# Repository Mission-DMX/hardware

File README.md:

# hardware
This repository contains documentations, pcb designs and fpga designs of the console

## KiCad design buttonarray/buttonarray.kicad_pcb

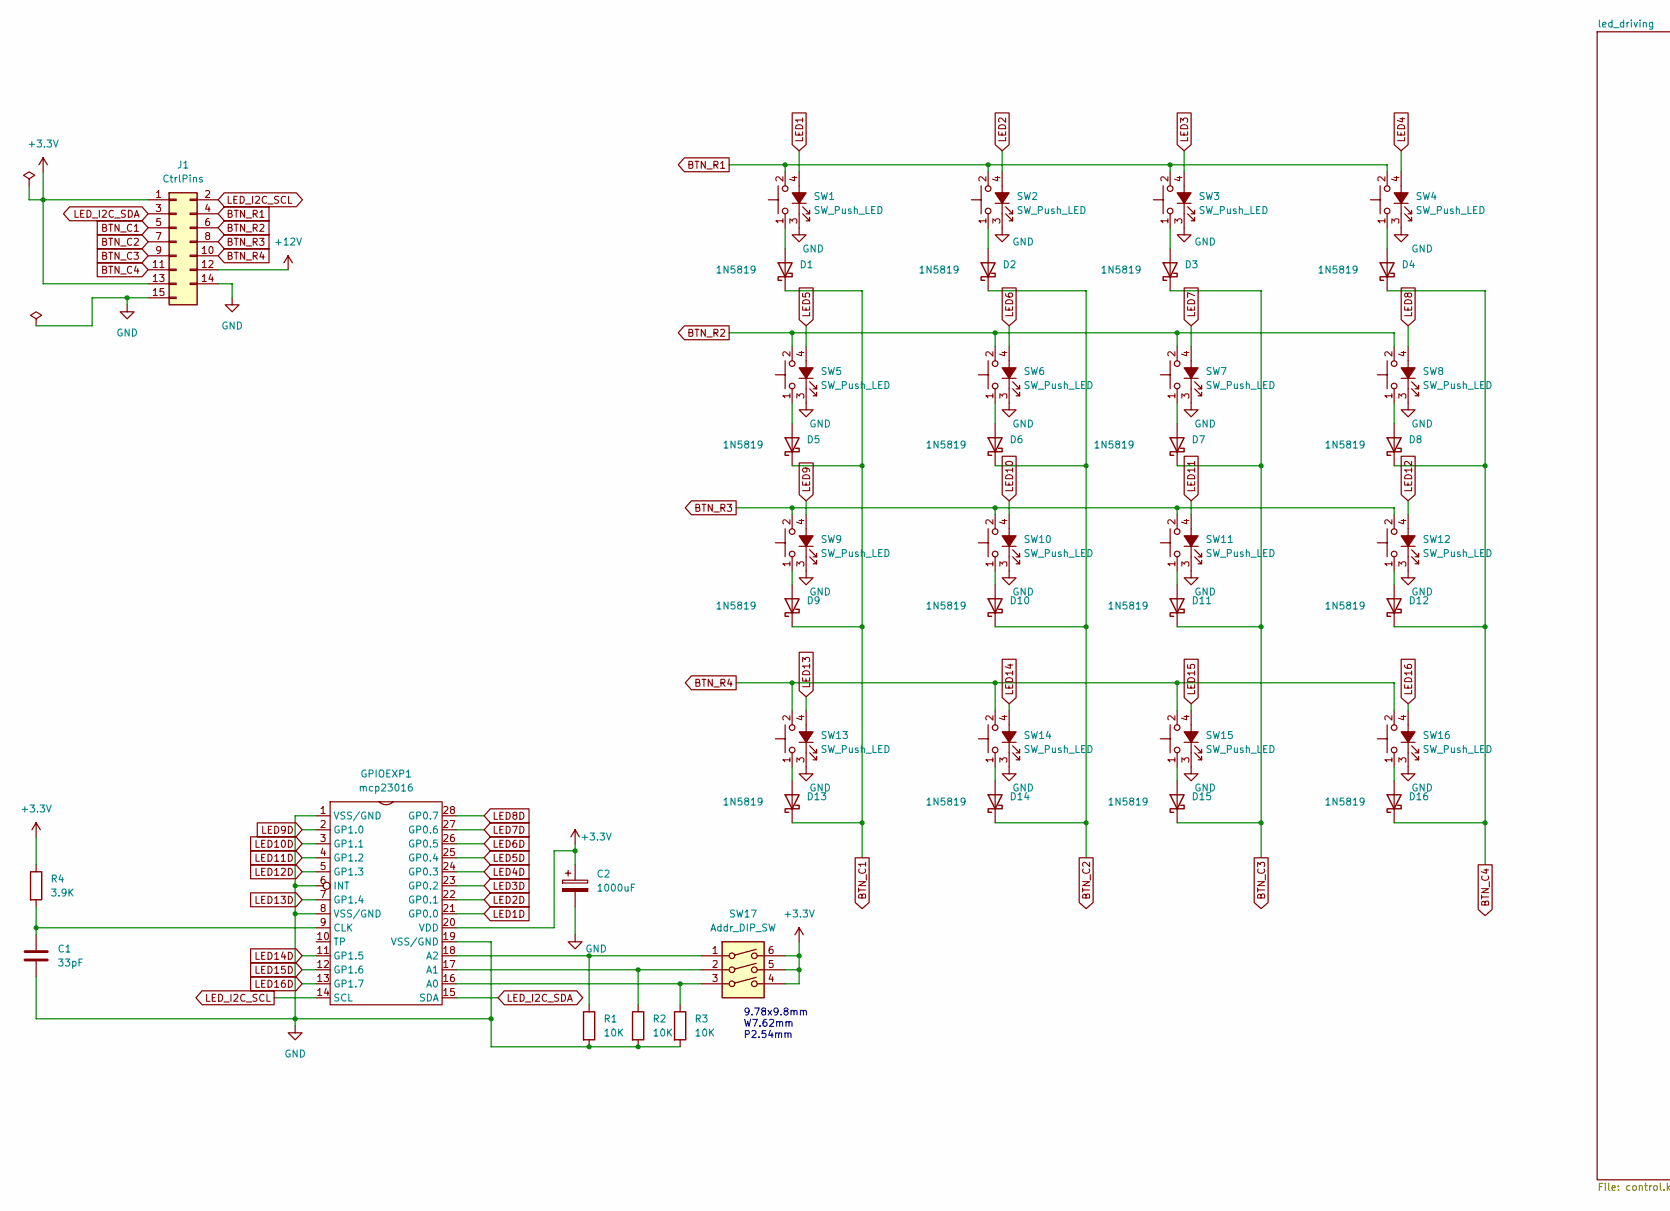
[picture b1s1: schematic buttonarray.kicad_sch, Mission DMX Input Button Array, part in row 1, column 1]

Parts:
C1: 33pF; C_1206_3216Metric_Pad1.33x1.80mm_HandSolder
C2: 1000uF; CP_Radial_D13.0mm_P5.00mm
D1, D2, D3, D4, D5, D6, D7, D8, D9, D10, D11, D12, D13, D14, D15, D16: 1N5819; D_DO-41_SOD81_P10.16mm_Horizontal
GPIOEXP1: mcp23016
J1: CtrlPins; IDC-Header_2x08_P2.54mm_Latch_Vertical
R1, R2, R3: 10K; R_0805_2012Metric_Pad1.20x1.40mm_HandSolder
R4: 3.9K; R_0603_1608Metric_Pad0.98x0.95mm_HandSolder
SW1, SW2, SW3, SW4, SW5, SW6, SW7, SW8, SW9, SW10, SW11, SW12, SW13, SW14, SW15, SW16: SW_Push_LED; MXOnly-1U
SW17: Addr_DIP_SW; SW_DIP_SPSTx03_Slide_9.78x9.8mm_W7.62mm_P2.54mm

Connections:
+3V3: C2.1, GPIOEXP1.20 (VDD), J1.1, J1.13, R4.1, SW17.4, SW17.5, SW17.6; also elsewhere on the board
+12V: J1.12; also elsewhere on the board
BTN_C1: D1.1 (K), D5.1 (K), D9.1 (K), D13.1 (K), J1.5
BTN_C2: D2.1 (K), D6.1 (K), D10.1 (K), D14.1 (K), J1.7
BTN_C3: D3.1 (K), D7.1 (K), D11.1 (K), D15.1 (K), J1.9
BTN_C4: D4.1 (K), D8.1 (K), D12.1 (K), D16.1 (K), J1.11
BTN_R1: J1.4, SW1.2, SW2.2, SW3.2, SW4.2
BTN_R2: J1.6, SW5.2, SW6.2, SW7.2, SW8.2
BTN_R3: J1.8, SW9.2, SW10.2, SW11.2, SW12.2
BTN_R4: J1.10, SW13.2, SW14.2, SW15.2, SW16.2
GND: C1.2, C2.2, GPIOEXP1.1 (VSS/GND), GPIOEXP1.6 (INT), GPIOEXP1.8 (VSS/GND), GPIOEXP1.19 (VSS/GND), J1.14, J1.15, R1.2, R2.2, R3.2, SW1.3 (K), SW2.3 (K), SW3.3 (K), SW4.3 (K), SW5.3 (K), SW6.3 (K), SW7.3 (K), SW8.3 (K), SW9.3 (K), SW10.3 (K), SW11.3 (K), SW12.3 (K), SW13.3 (K), SW14.3 (K), SW15.3 (K), SW16.3 (K); also elsewhere on the board
LED1: SW1.4 (A); also elsewhere on the board
LED1D: GPIOEXP1.21 (GP0.0); also elsewhere on the board
LED2: SW2.4 (A); also elsewhere on the board
LED2D: GPIOEXP1.22 (GP0.1); also elsewhere on the board
LED3: SW3.4 (A); also elsewhere on the board
LED3D: GPIOEXP1.23 (GP0.2); also elsewhere on the board
LED4: SW4.4 (A); also elsewhere on the board
LED4D: GPIOEXP1.24 (GP0.3); also elsewhere on the board
LED5: SW5.4 (A); also elsewhere on the board
LED5D: GPIOEXP1.25 (GP0.4); also elsewhere on the board
LED6: SW6.4 (A); also elsewhere on the board
LED6D: GPIOEXP1.26 (GP0.5); also elsewhere on the board
LED7: SW7.4 (A); also elsewhere on the board
LED7D: GPIOEXP1.27 (GP0.6); also elsewhere on the board
LED8: SW8.4 (A); also elsewhere on the board
LED8D: GPIOEXP1.28 (GP0.7); also elsewhere on the board
LED9: SW9.4 (A); also elsewhere on the board
LED9D: GPIOEXP1.2 (GP1.0); also elsewhere on the board
LED10: SW10.4 (A); also elsewhere on the board
LED10D: GPIOEXP1.3 (GP1.1); also elsewhere on the board
LED11: SW11.4 (A); also elsewhere on the board
LED11D: GPIOEXP1.4 (GP1.2); also elsewhere on the board
LED12: SW12.4 (A); also elsewhere on the board
LED12D: GPIOEXP1.5 (GP1.3); also elsewhere on the board
LED13: SW13.4 (A); also elsewhere on the board
LED13D: GPIOEXP1.7 (GP1.4); also elsewhere on the board
LED14: SW14.4 (A); also elsewhere on the board
LED14D: GPIOEXP1.11 (GP1.5); also elsewhere on the board
LED15: SW15.4 (A); also elsewhere on the board
LED15D: GPIOEXP1.12 (GP1.6); also elsewhere on the board
LED16: SW16.4 (A); also elsewhere on the board
LED16D: GPIOEXP1.13 (GP1.7); also elsewhere on the board
LED_I2C_SCL: GPIOEXP1.14 (SCL), J1.2
LED_I2C_SDA: GPIOEXP1.15 (SDA), J1.3
unnamed: C1.1, GPIOEXP1.9 (CLK), R4.2
unnamed: D1.2 (A), SW1.1
unnamed: D2.2 (A), SW2.1
unnamed: D3.2 (A), SW3.1
unnamed: D4.2 (A), SW4.1
unnamed: D5.2 (A), SW5.1
unnamed: D6.2 (A), SW6.1
unnamed: D7.2 (A), SW7.1
unnamed: D8.2 (A), SW8.1
unnamed: D9.2 (A), SW9.1
unnamed: D10.2 (A), SW10.1
unnamed: D11.2 (A), SW11.1
unnamed: D12.2 (A), SW12.1
unnamed: D13.2 (A), SW13.1
unnamed: D14.2 (A), SW14.1
unnamed: D15.2 (A), SW15.1
unnamed: D16.2 (A), SW16.1
unnamed: GPIOEXP1.16 (A0), R3.1, SW17.3
unnamed: GPIOEXP1.17 (A1), R2.1, SW17.2
unnamed: GPIOEXP1.18 (A2), R1.1, SW17.1

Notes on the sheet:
9.78x9.8mm W7.62mm P2.54mm

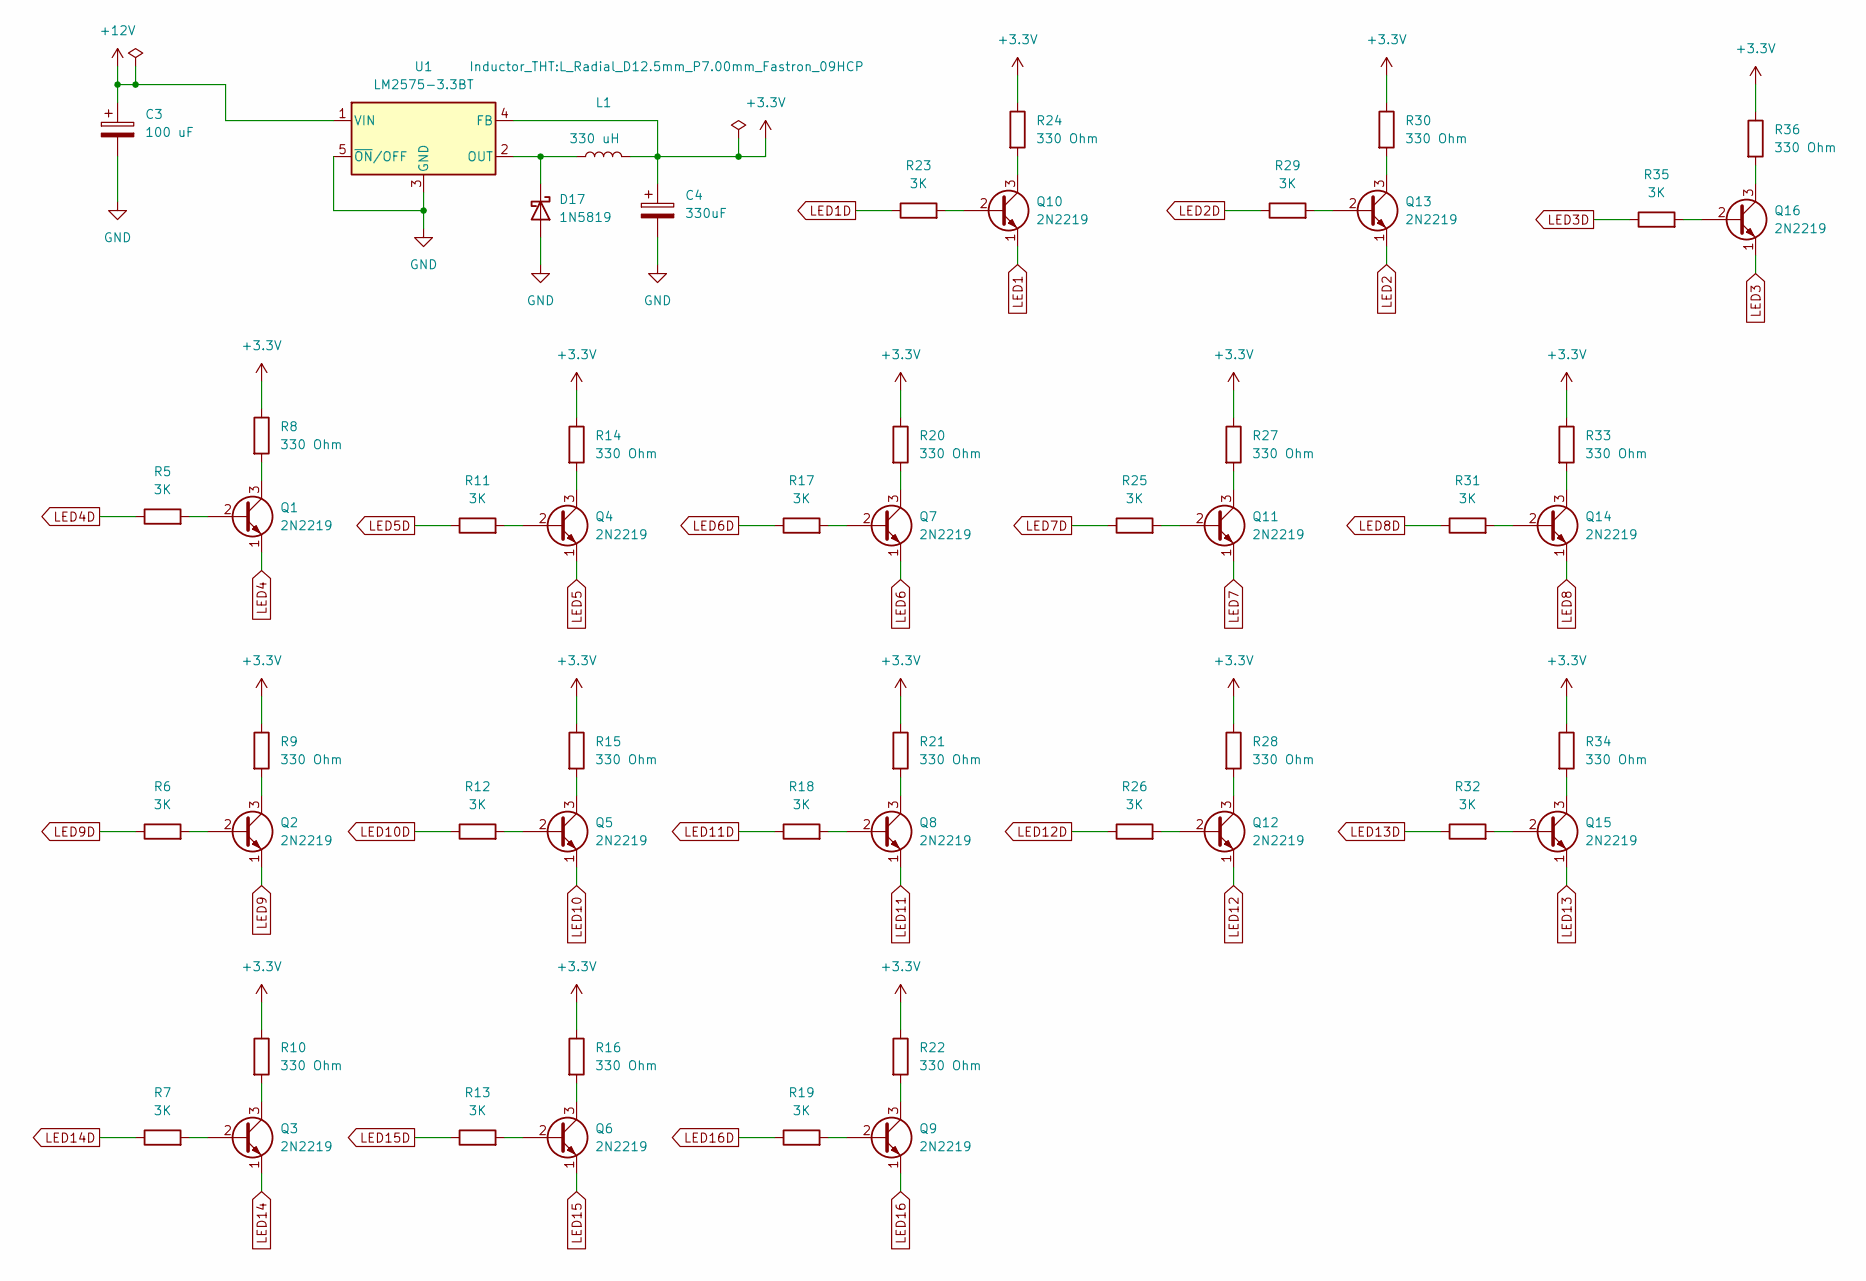
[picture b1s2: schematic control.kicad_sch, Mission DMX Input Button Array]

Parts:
C3: 100 uF; CP_Radial_D6.3mm_P2.50mm
C4: 330uF; CP_Radial_D10.0mm_P5.00mm
D17: 1N5819; D_DO-41_SOD81_P10.16mm_Horizontal
L1: 330 uH; L_Radial_D12.5mm_P7.00mm_Fastron_09HCP
Q1, Q2, Q3, Q4, Q5, Q6, Q7, Q8, Q9, Q10, Q11, Q12, Q13, Q14, Q15, Q16: 2N2219; TO-39-3
R5, R6, R7, R11, R12, R13, R17, R18, R19, R23, R25, R26, R29, R31, R32, R35: 3K; R_1206_3216Metric_Pad1.30x1.75mm_HandSolder
R8, R9, R10, R14, R15, R16, R20, R21, R22, R24, R27, R28, R30, R33, R34, R36: 330 Ohm; R_1206_3216Metric_Pad1.30x1.75mm_HandSolder
U1: LM2575-3.3BT; TO-220-5_Vertical

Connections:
+3V3: C4.1, L1.2, R8.1, R9.1, R10.1, R14.1, R15.1, R16.1, R20.1, R21.1, R22.1, R24.1, R27.1, R28.1, R30.1, R33.1, R34.1, R36.1, U1.4 (FB); also elsewhere on the board
+12V: C3.1, U1.1 (VIN); also elsewhere on the board
GND: C3.2, C4.2, D17.2 (A), U1.3 (GND), U1.5 (~ON/OFF); also elsewhere on the board
LED1: Q10.1 (E); also elsewhere on the board
LED1D: R23.1; also elsewhere on the board
LED2: Q13.1 (E); also elsewhere on the board
LED2D: R29.1; also elsewhere on the board
LED3: Q16.1 (E); also elsewhere on the board
LED3D: R35.1; also elsewhere on the board
LED4: Q1.1 (E); also elsewhere on the board
LED4D: R5.1; also elsewhere on the board
LED5: Q4.1 (E); also elsewhere on the board
LED5D: R11.1; also elsewhere on the board
LED6: Q7.1 (E); also elsewhere on the board
LED6D: R17.1; also elsewhere on the board
LED7: Q11.1 (E); also elsewhere on the board
LED7D: R25.1; also elsewhere on the board
LED8: Q14.1 (E); also elsewhere on the board
LED8D: R31.1; also elsewhere on the board
LED9: Q2.1 (E); also elsewhere on the board
LED9D: R6.1; also elsewhere on the board
LED10: Q5.1 (E); also elsewhere on the board
LED10D: R12.1; also elsewhere on the board
LED11: Q8.1 (E); also elsewhere on the board
LED11D: R18.1; also elsewhere on the board
LED12: Q12.1 (E); also elsewhere on the board
LED12D: R26.1; also elsewhere on the board
LED13: Q15.1 (E); also elsewhere on the board
LED13D: R32.1; also elsewhere on the board
LED14: Q3.1 (E); also elsewhere on the board
LED14D: R7.1; also elsewhere on the board
LED15: Q6.1 (E); also elsewhere on the board
LED15D: R13.1; also elsewhere on the board
LED16: Q9.1 (E); also elsewhere on the board
LED16D: R19.1; also elsewhere on the board
unnamed: D17.1 (K), L1.1, U1.2 (OUT)
unnamed: Q1.2 (B), R5.2
unnamed: Q1.3 (C), R8.2
unnamed: Q2.2 (B), R6.2
unnamed: Q2.3 (C), R9.2
unnamed: Q3.2 (B), R7.2
unnamed: Q3.3 (C), R10.2
unnamed: Q4.2 (B), R11.2
unnamed: Q4.3 (C), R14.2
unnamed: Q5.2 (B), R12.2
unnamed: Q5.3 (C), R15.2
unnamed: Q6.2 (B), R13.2
unnamed: Q6.3 (C), R16.2
unnamed: Q7.2 (B), R17.2
unnamed: Q7.3 (C), R20.2
unnamed: Q8.2 (B), R18.2
unnamed: Q8.3 (C), R21.2
unnamed: Q9.2 (B), R19.2
unnamed: Q9.3 (C), R22.2
unnamed: Q10.2 (B), R23.2
unnamed: Q10.3 (C), R24.2
unnamed: Q11.2 (B), R25.2
unnamed: Q11.3 (C), R27.2
unnamed: Q12.2 (B), R26.2
unnamed: Q12.3 (C), R28.2
unnamed: Q13.2 (B), R29.2
unnamed: Q13.3 (C), R30.2
unnamed: Q14.2 (B), R31.2
unnamed: Q14.3 (C), R33.2
unnamed: Q15.2 (B), R32.2
unnamed: Q15.3 (C), R34.2
unnamed: Q16.2 (B), R35.2
unnamed: Q16.3 (C), R36.2

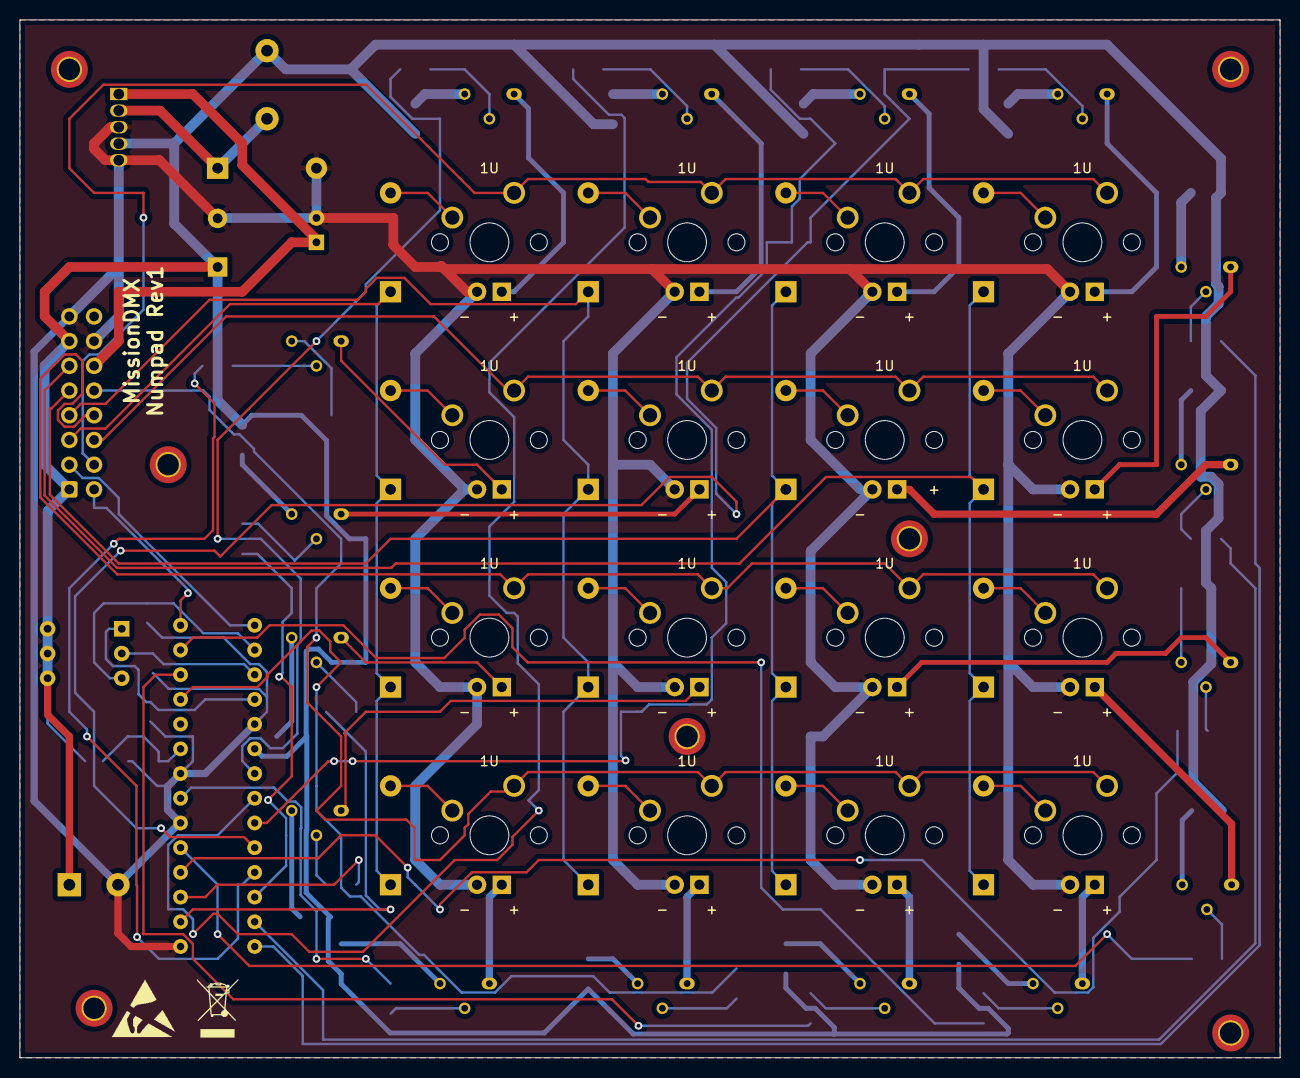
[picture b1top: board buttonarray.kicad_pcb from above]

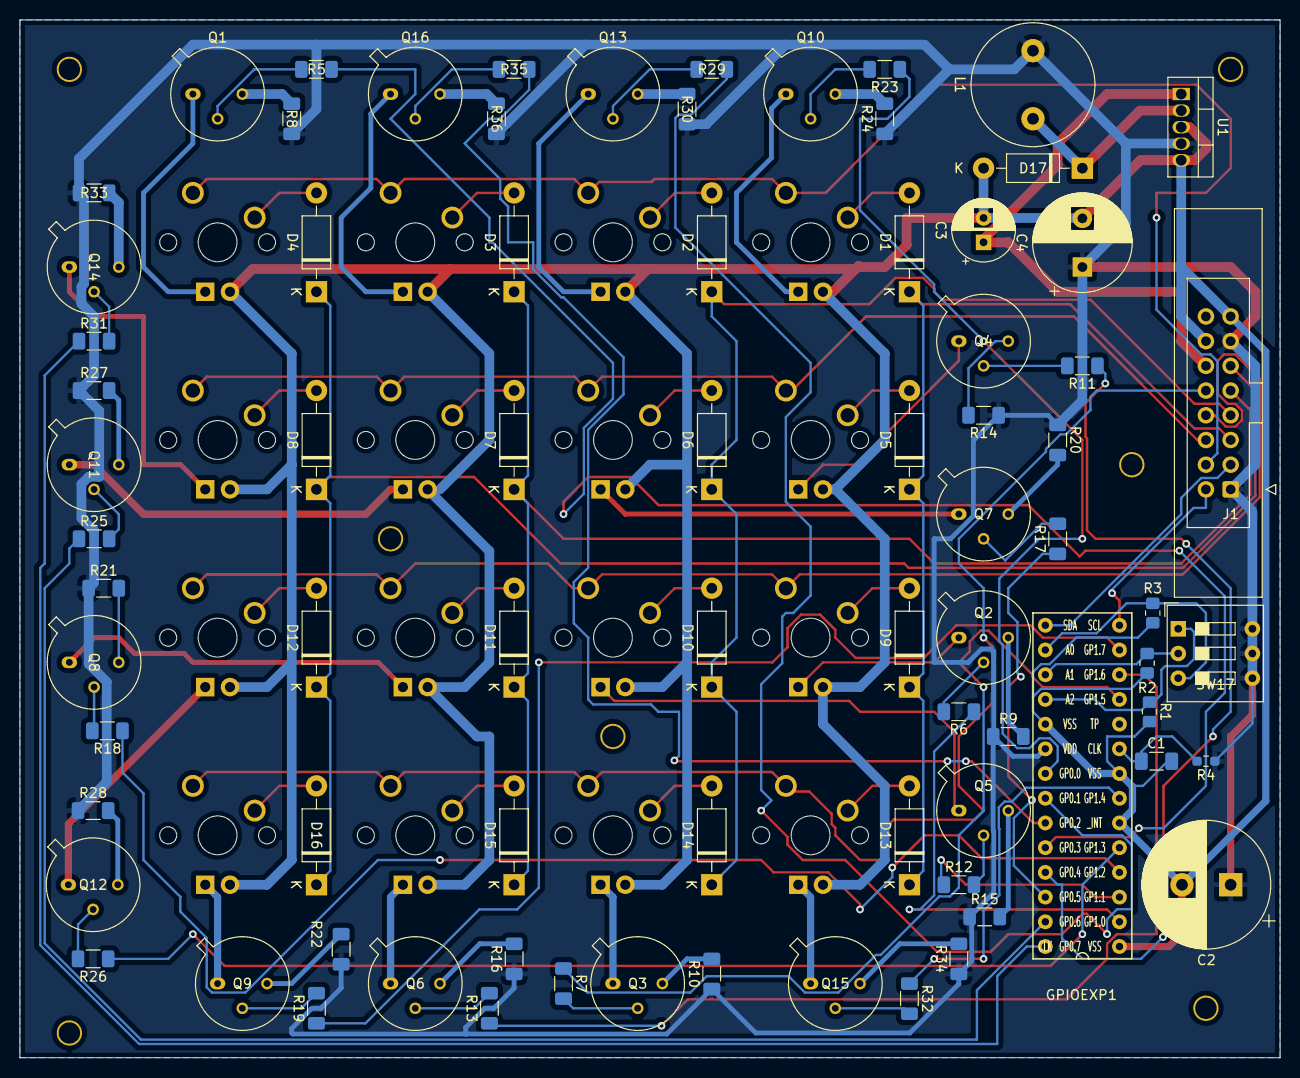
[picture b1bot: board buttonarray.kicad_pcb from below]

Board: 2 copper layers, 129.5 x 106.7 mm, 94 parts (78 on the bottom side), 98 nets.

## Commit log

2022-10-24 add: licenses
2022-10-24 add: first revion of button array schematic
2022-11-15 add: led drivers
2023-03-07 add: footprints for button array except switches
2023-11-13 add: key footprint
2023-11-13 add: key footprint mapping
2023-11-13 fix: missing dip switch footprint
2023-11-13 add: component placement for numpad
2023-11-13 chg: component text positions
2023-11-13 add: numpad routing prototype
2023-11-13 fix: drill distances
2023-11-13 fix: missing ground plane
2023-11-17 chg: button array rev 1
2023-11-23 add: mainboard sch files
2023-11-26 add: first step towards mcu firmware
2023-12-10 chg: firmware prototype
2025-01-16 add: LICENSE for the microcontroller firmware
2025-01-16 add: LICENSE to test scripts
2025-01-16 add: SPDX ID in power_supply_test.py
2025-01-16 add: general LICENSE
2025-01-16 add: default case to LICENSE
2025-03-17 add: dir
2025-03-20 Version mit Sendern, Empfänger und neue Nachricht erkennenung
2025-05-26 Version 26.5.
2025-08-14 state maschine input controller
2025-08-14 Input Controller State maschine bearbeitet
2025-08-22 State Machine eingefügt und verbunden
2026-01-25 add: initial fpga design for mainboard
2026-01-26 fix: mainboard fpga clock mgmt
2026-01-27 add: ddr3 io bus
